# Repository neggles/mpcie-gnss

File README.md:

# mPCIe-GNSS (mPCIe-LC6L)  

This is a little miniPCIe card I designed to hold a [Quectel LC86L](https://www.quectel.com/product/gnss-lc86l/) GNSS module, with a timepulse header and a backup supercap.

## Repository Structure
- `mPCIe-GNSS` contains the main schematics and board drawing
- `mPCIe-GNSS/mPCIe-GNSS.pretty` contains the board-specific footprints
- `mPCIe-GNSS/mPCIe-GNSS-archive.lib` contains the board-specific symbols

I had this made by [JLCPCB](https://jlcpcb.com) using their 1mm thick PCBs, and elected to get them to assemble most of it - while all of the parts except the supercapacitor, connectors, and GNSS module are in their extended part library, it didn't make sense to spend $6 on extended part fees for two assembled boards, so I skipped the transistors and diode.

## Building
Simply call `make` in the top-top level directory. The `build` directory will
them contain:

- the main mPCIe board
- A panelized version of said board
- zipped gerbers for the boards you can directly use for manufacturing
- zipped gerbers and SMT assembly BOM/position files for JLCPCB's SMT assembly service for the single-board version.

Makefile uses [Jan Mrázek](https://github.com/yaqwsx)'s [KiKit](https://github.com/yaqwsx/KiKit), which I cannot recommend enough, and therefore has to be available on your system.

Jan's [jlcparts](https://yaqwsx.github.io/jlcparts/) app was also extremely useful in narrowing down part choices based on what JLCPCB have available.

-----
### **IMPORTANT NOTE:** If you give JLCPCB these files as-is, *please* verify the orientation of every part before submitting.

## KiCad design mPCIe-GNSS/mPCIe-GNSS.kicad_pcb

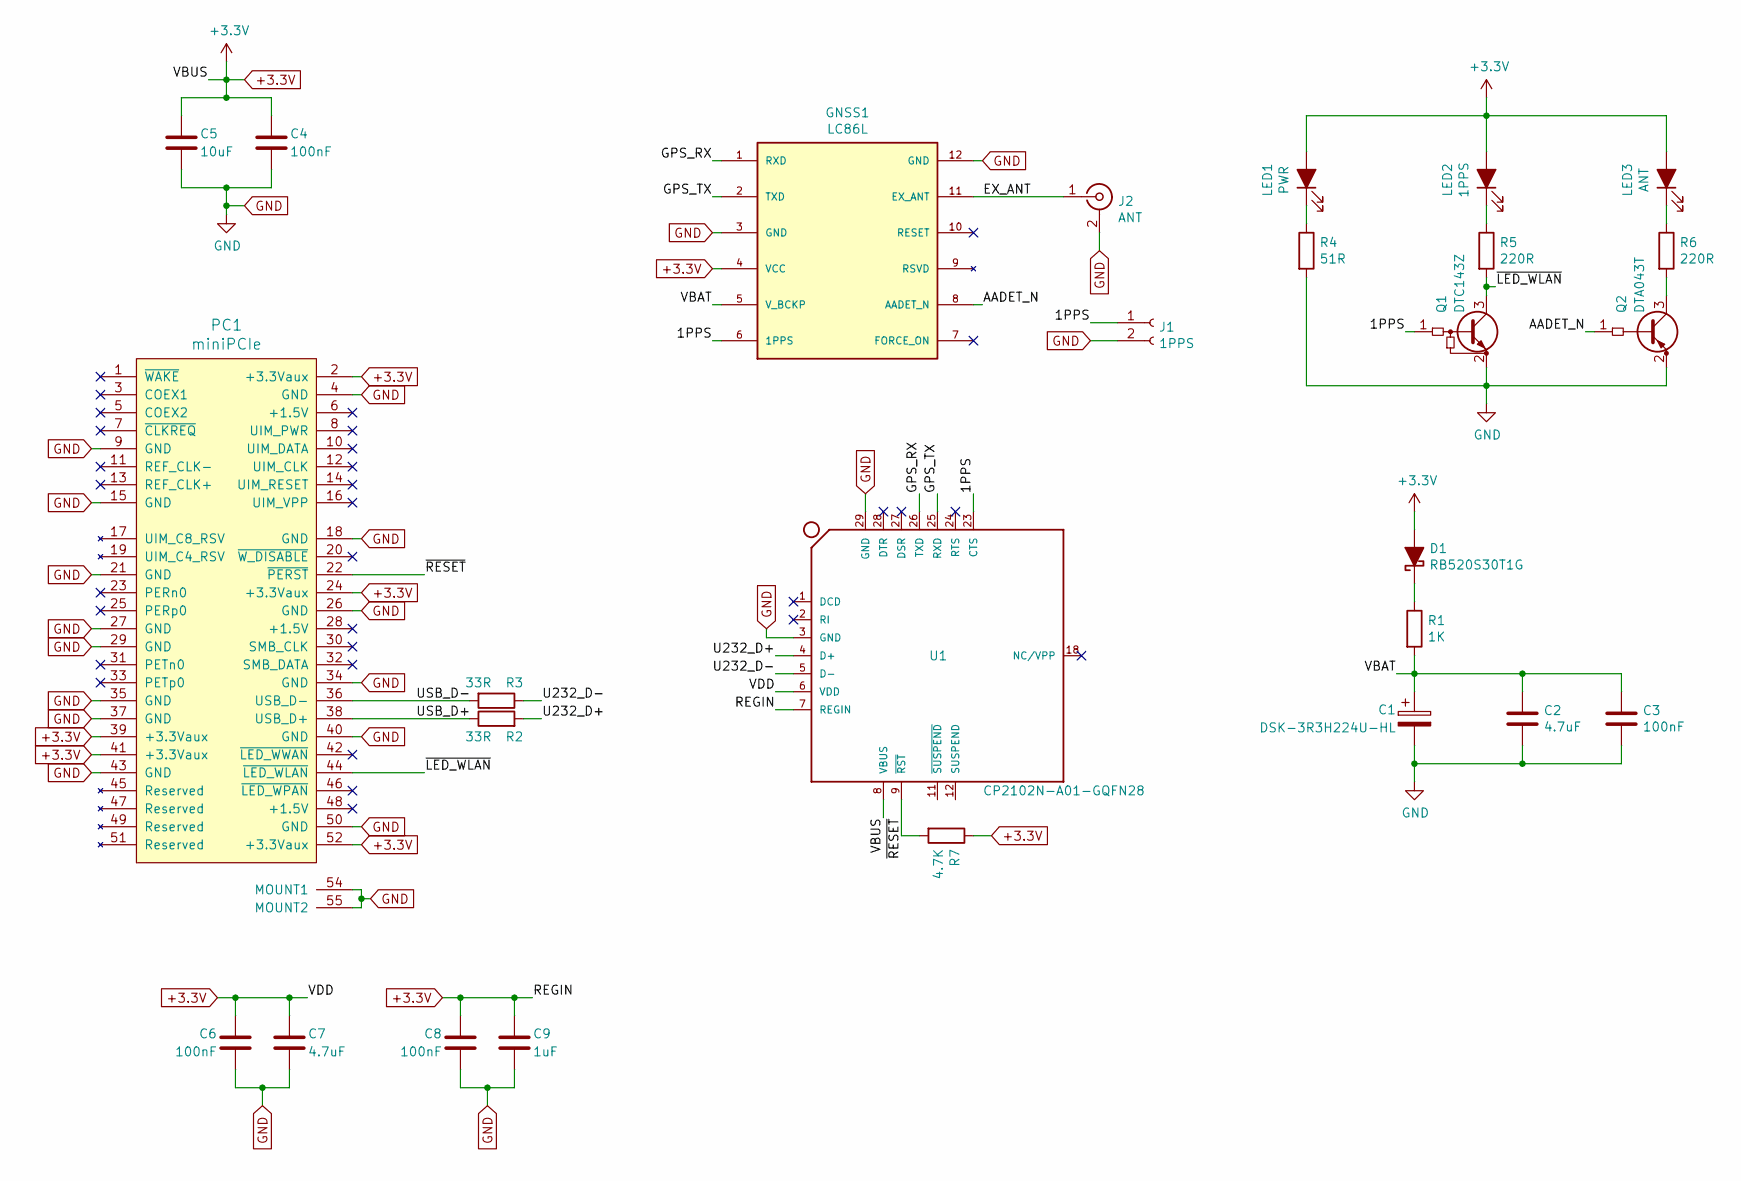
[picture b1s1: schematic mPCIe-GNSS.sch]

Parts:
C1: DSK-3R3H224U-HL; CAP_DSK-3R3H224U-HL
C2, C7: 4.7uF; C_0402_1005Metric; LCSC C23733
C3, C4, C6, C8: 100nF; C_0402_1005Metric; LCSC C1525
C5: 10uF; C_0402_1005Metric; LCSC C15525
C9: 1uF; C_0402_1005Metric; LCSC C52923
D1: RB520S30T1G; D_SOD-523; LCSC C154821
GNSS1: LC86L; XCVR_LC86L
J1: 1PPS; JST_SH_SM02B-SRSS-TB_1x02-1MP_P1.00mm_Horizontal_3D
J2: ANT; U.FL_Hirose_U.FL-R-SMT-1_Vertical
LED1: PWR; LED_0603_1608Metric_SnapModel; LCSC C72041
LED2: 1PPS; LED_0603_1608Metric_SnapModel; LCSC C72038
LED3: ANT; LED_0603_1608Metric_SnapModel; LCSC C72043
PC1: miniPCIe; mini-PCIe_F1_Full_v517
Q1: DTC143Z; Q_EMT3F
Q2: DTA043T; Q_EMT3F
R1: 1K; R_0402_1005Metric; LCSC C11702
R2, R3: 33R; R_0402_1005Metric; LCSC C25105
R4: 51R; R_0402_1005Metric; LCSC C25125
R5, R6: 220R; R_0402_1005Metric; LCSC C25091
R7: 4.7K; R_0402_1005Metric; LCSC C25900
U1: CP2102N-A01-GQFN28; QFN28G_0.5-5X5MM; MPN CP2102-GMR; LCSC C6568

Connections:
+3.3V: C4.1, C5.2, C6.2, C7.1, C8.2, C9.1, D1.2 (A), GNSS1.4 (VCC), LED1.2 (A), LED2.2 (A), LED3.2 (A), PC1.2 (+3.3Vaux), PC1.24 (+3.3Vaux), PC1.39 (+3.3Vaux), PC1.41 (+3.3Vaux), PC1.52 (+3.3Vaux), R7.1, U1.6 (VDD), U1.7 (REGIN), U1.8 (VBUS)
/1PPS: GNSS1.6 (1PPS), J1.1, Q1.1 (B), U1.23 (CTS)
/AADET_N: GNSS1.8 (AADET_N), Q2.1 (B)
/EX_ANT: GNSS1.11 (EX_ANT), J2.1 (In)
/GPS_RX: GNSS1.1 (RXD), U1.26 (TXD)
/GPS_TX: GNSS1.2 (TXD), U1.25 (RXD)
/U232_D+: R2.2, U1.4 (D+)
/U232_D-: R3.1, U1.5 (D-)
/USB_D+: PC1.38 (USB_D+), R2.1
/USB_D-: PC1.36 (USB_D-), R3.2
/VBAT: C1.1, C2.1, C3.1, GNSS1.5 (V_BCKP), R1.2
/~LED_WLAN: PC1.44 (~LED_WLAN), Q1.3 (C), R5.2
/~RESET: PC1.22 (~PERST), R7.2, U1.9 (~RST)
GND: C1.2, C2.2, C3.2, C4.2, C5.1, C6.1, C7.2, C8.1, C9.2, GNSS1.3 (GND), GNSS1.12 (GND), J1.2, J2.2 (Ext), PC1.4 (GND), PC1.9 (GND), PC1.15 (GND), PC1.18 (GND), PC1.21 (GND), PC1.26 (GND), PC1.27 (GND), PC1.29 (GND), PC1.34 (GND), PC1.35 (GND), PC1.37 (GND), PC1.40 (GND), PC1.43 (GND), PC1.50 (GND), PC1.54 (MOUNT1), PC1.55 (MOUNT2), Q1.2 (E), Q2.2 (E), R4.2, U1.3 (GND), U1.29 (GND)
unnamed: D1.1 (K), R1.1
unnamed: LED1.1 (K), R4.1
unnamed: LED2.1 (K), R5.1
unnamed: LED3.1 (K), R6.1
unnamed: Q2.3 (C), R6.2

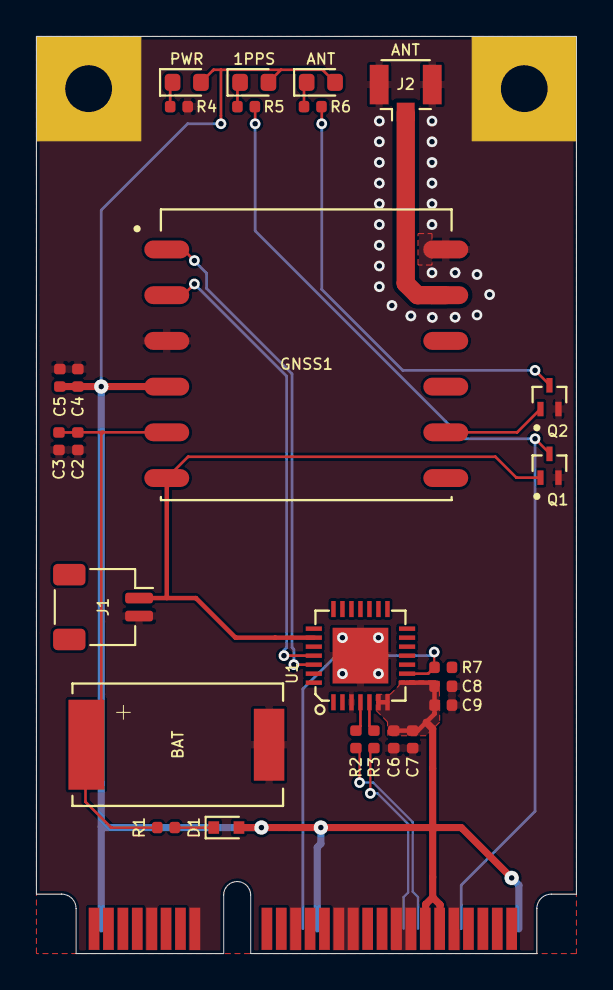
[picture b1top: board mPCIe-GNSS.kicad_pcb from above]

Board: 2 copper layers, 30.0 x 51.0 mm, 27 parts (0 on the bottom side), 19 nets.

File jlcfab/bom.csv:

Comment,Designator,Footprint,LCSC
RB520S30T1G,D1,Diode_SMD:D_SOD-523,C154821
4.7uF,"C2,C7",Capacitor_SMD:C_0402_1005Metric,C23733
100nF,"C3,C6,C4,C8",Capacitor_SMD:C_0402_1005Metric,C1525
1K,R1,Resistor_SMD:R_0402_1005Metric,C11702
1PPS,LED2,1 My Footprints:LED_0603_1608Metric_SnapModel,C72038
220R,"R6,R5",Resistor_SMD:R_0402_1005Metric,C25091
51R,R4,Resistor_SMD:R_0402_1005Metric,C25125
PWR,LED1,1 My Footprints:LED_0603_1608Metric_SnapModel,C72041
ANT,LED3,1 My Footprints:LED_0603_1608Metric_SnapModel,C72043
33R,"R2,R3",Resistor_SMD:R_0402_1005Metric,C25105
10uF,C5,Capacitor_SMD:C_0402_1005Metric,C15525
CP2102N-A01-GQFN28,U1,QFN28G_0.5-5X5MM,C6568
1uF,C9,Capacitor_SMD:C_0402_1005Metric,C52923
4.7K,R7,Resistor_SMD:R_0402_1005Metric,C25900

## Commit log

2021-01-23 first ver
2021-01-23 version 0.2
2021-01-23 version 0.3
2021-01-23 trim a file or three
2021-01-23 add gitignore
2021-01-23 license
2021-01-23 initial readme update
2021-07-02 restructure
2021-07-02 Initial gh-pages commit
2021-07-02 Deploying to gh-pages from @ neg2led/mpcie-gnss@bd1ff46c51f71233c7135996375c3902f1b9400a 🚀
2021-07-02 remove missing assets from makefile
